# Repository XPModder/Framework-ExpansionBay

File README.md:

# Framework-ExpansionBay
Some stuff I made for the Framework Laptop 16 Expansion Bay

# Disclaimer
The Expansion Bay specification was created by Framework Computer Inc and published under Creative Commons BY 4.0 (http://creativecommons.org/licenses/by/4.0/)

All Contents of this repository are provided as-is. I take no responsibility for any damages caused to your device(s) by any content of this repository!

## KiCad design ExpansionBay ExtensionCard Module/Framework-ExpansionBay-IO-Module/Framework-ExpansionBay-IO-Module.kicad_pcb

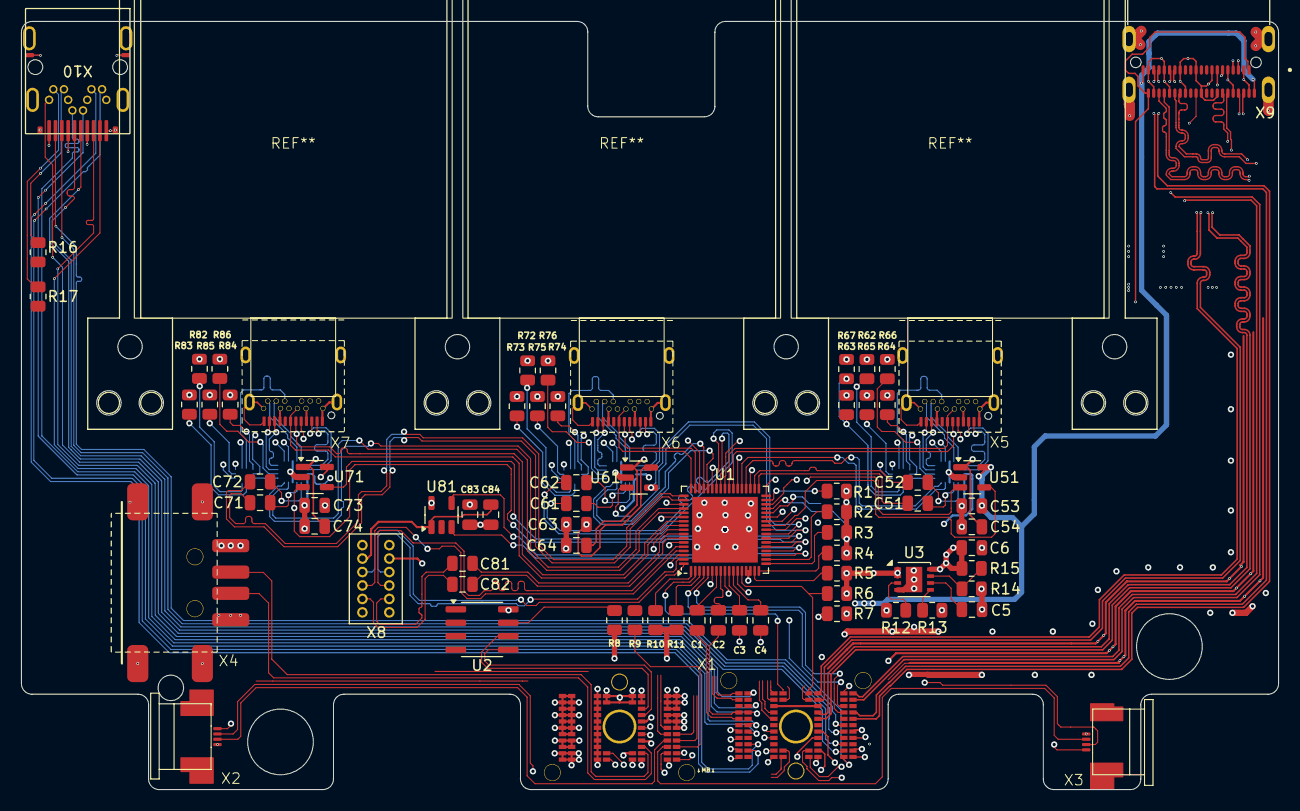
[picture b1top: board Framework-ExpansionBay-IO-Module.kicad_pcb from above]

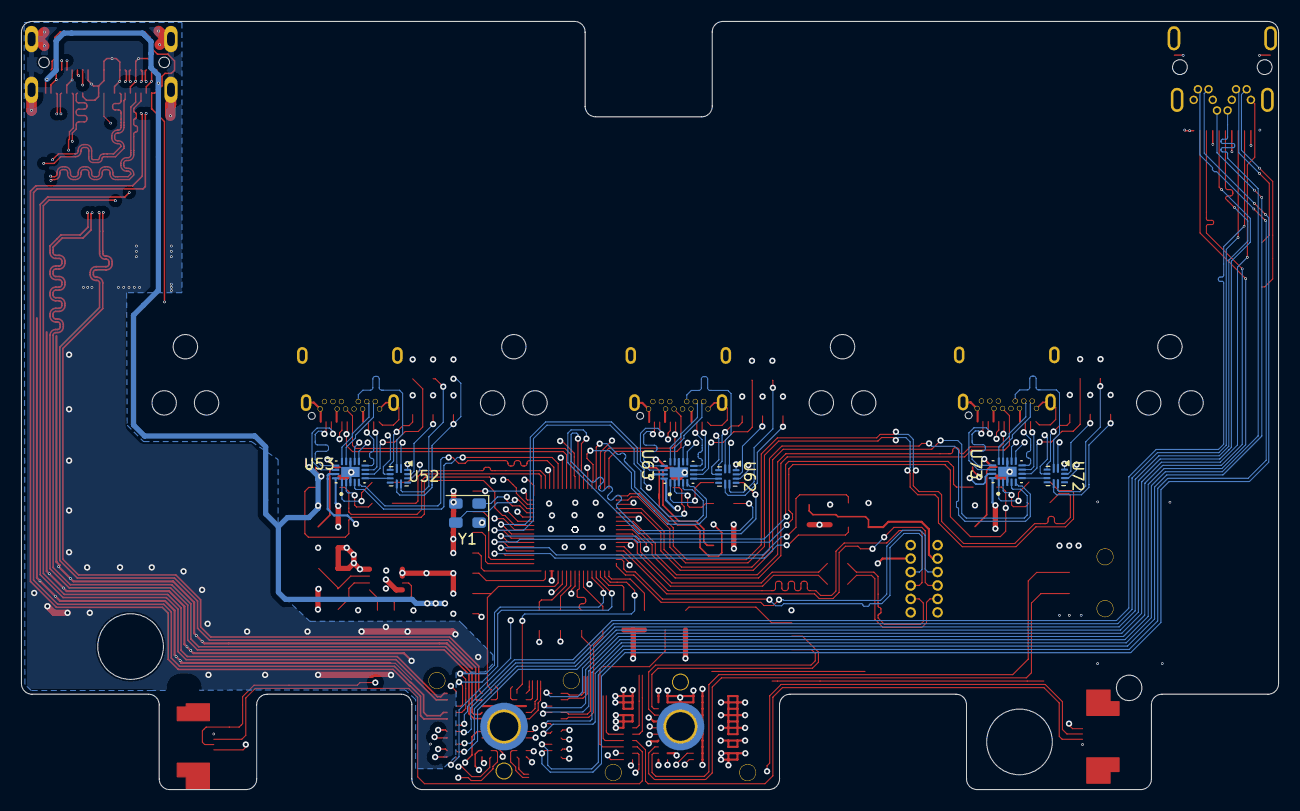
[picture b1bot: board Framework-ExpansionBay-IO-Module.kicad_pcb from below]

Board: 4 copper layers, 118.7 x 72.5 mm, 79 parts (7 on the bottom side), 164 nets.

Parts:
C1, C2, C3, C4, C51, C52, C53, C54, C61, C62, C63, C64, C71, C72, C73, C74, C81, C82, C83, C84: 100n; C_0805_2012Metric
C5, C6: 1u; C_0805_2012Metric
R1: 1k60; R_0805_2012Metric
R2, R3, R4, R6, R10, R11, R12, R13, R14, R16, R17: 10k; R_0805_2012Metric
R5: 47k; R_0805_2012Metric
R7, R9: 330k; R_0805_2012Metric
R8, R62, R63, R64, R65, R66, R67, R72, R73, R74, R75, R76, R82, R83, R84, R85, R86: 100k; R_0805_2012Metric
R15: 15k-16k; R_0805_2012Metric
U1: UPD720201K8-701-BAC-A; QFN-68-1EP_8x8mm_P0.4mm_EP6.2x6.2mm
U2: 24LC32A-I/SN; SOIC-8_3.9x4.9mm_P1.27mm
U3: MCP1727-ADJxMF; DFN-8-1EP_3x3mm_P0.65mm_EP1.55x2.4mm
U51, U61, U71, U81: XC8107; SOT-23-5
U52, U62, U72: FUSB303BTMX; Texas_X2QFN-12_1.6x1.6mm_P0.4mm
U53, U63, U73: FUSB340TMX; QFN40P200X280X40-19N
X1: Framework-FX-Beam
X2: Fan0; Molex-52746-0471
X3: Fan1; Molex-52746-0471
X4: USB_A; Würth-USB2-629104190121
X5, X6, X7: USB_C_Receptacle; Amphenol-USBC-10137062-00021LF
X8: Expansion-USB3; DS1015-02-12R6
X9: Molex-SFF8612-OcuLink-1719821142; MOLEX_1719821142
X10: FOXCONN 3VM11201-D730-7H; Mini DP FOXCONN 3VM11201-D730-7H
Y1: 24MHz; Crystal_SMD_EuroQuartz_MT-4Pin_3.2x2.5mm

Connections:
+1V0: C6.2, R15.2, U1.9 (VDD10), U1.12 (VDD10), U1.28 (VDD10), U1.37 (VDD10), U1.43 (VDD10), U1.46 (VDD10), U1.54 (VDD10), U1.60 (VDD10), U1.63 (VDD10), U3.8 (Vout)
+3V3: R5.2, R6.2, R8.2, R10.2, R11.2, R12.2, R13.2, R62.1, R63.2, R64.2, R72.1, R73.2, R74.2, R82.1, R83.2, R84.2, U1.6 (AVDD33), U1.14 (PONRSTB), U1.15 (VDD33), U1.29 (VDD33), U1.32 (AVDD33), U1.40 (VDD33), U1.49 (VDD33), U1.57 (VDD33), U1.66 (VDD33), U2.8 (VCC), U3.1 (Vin), U3.2 (Vin), U52.12 (VDD), U53.17 (VDD), U62.12 (VDD), U63.17 (VDD), U72.12 (VDD), U73.17 (VDD), X1.P-34 (3.3V_ALW), X1.P-35 (3.3V_ALW), X1.P-38 (3.3V_ALW), X1.P-39 (3.3V_ALW), X8.11, X9.A1 (3V3), X9.B21 (3V3), X10.20 (DP_PWR)
+5V: C53.2, C63.2, C73.2, C83.2, U51.5 (IN), U61.5 (IN), U71.5 (IN), U81.5 (IN), X1.P-10 (5V_ALW), X1.P-11 (5V_ALW), X1.P-21 (5V_ALW), X1.P-22 (5V_ALW), X4.1 (VBUS), X8.1, X8.12, X9.A21 (5V), X9.B1 (5V)
+12V: X1.P-41 (12V_Fan), X2.1, X3.1
DP_AUX+: X1.D-21 (DP_A_AUX), X10.16 (AUXp)
DP_AUX-: X1.D-20 (DP_A_AUX#), X10.18 (AUXn)
DP_HPD: X1.D-12 (DP_A_HPD), X10.2 (HPD)
DP_L0+: X1.D-18 (DP_A_L0), X10.12 (L3n(SRC)/L0p(SNK))
DP_L0-: X1.D-17 (DP_A_L0#), X10.10 (L3p(SRC)/L0n(SNK))
DP_L1+: X1.D-15 (DP_A_L1), X10.17 (L2n(SRC)/L1p(SNK))
DP_L1-: X1.D-14 (DP_A_L1#), X10.15 (L2p(SRC)/L1n(SNK))
DP_L2+: X1.D-62 (DP_A_L2), X10.11 (L1n(SRC)/L2p(SNK))
DP_L2-: X1.D-61 (DP_A_L2#), X10.9 (L1p(SRC)/L2n(SNK))
DP_L3+: X1.D-59 (DP_A_L3), X10.5 (L0n(SRC)/L3p(SNK))
DP_L3-: X1.D-58 (DP_A_L3#), X10.3 (L0p(SRC)/L3n(SNK))
Fan0_PWM: X1.P-60 (Fan0_SPEED), X2.3
Fan0_Speed: X1.P-37 (Fan0_PWM), X2.2
Fan1_PWM: X1.P-61 (Fan1_SPEED), X3.3
Fan1_Speed: X1.P-36 (Fan1_PWM), X3.2
GND: C5.1, C6.1, C53.1, C54.1, C63.1, C64.1, C73.1, C74.1, C83.1, C84.1, R1.1, R2.1, R3.1, R4.1, R7.2, R9.2, R14.1, R16.2, R17.2, R65.2, R66.2, R67.2, R75.2, R76.2, R85.2, R86.2, U1.34 (IC), U1.69 (GND), U2.1 (A0), U2.2 (A1), U2.3 (A2), U2.4 (GND), U3.4 (GND), U3.9 (GND), U51.2 (GND), U52.10 (GND), U53.3 (GND), U53.12 (GND), U53.18 (GND), U53.19 (EP), U61.2 (GND), U62.10 (GND), U63.3 (GND), U63.12 (GND), U63.18 (GND), U63.19 (EP), U71.2 (GND), U72.10 (GND), U73.3 (GND), U73.12 (GND), U73.18 (GND), U73.19 (EP), U81.2 (GND), X1.D-3 (GND), X1.D-6 (GND), X1.D-9 (GND), X1.D-13 (GND), X1.D-16 (GND), X1.D-19 (GND), X1.D-25 (GND), X1.D-28 (GND), X1.D-31 (GND), X1.D-44 (GND), X1.D-47 (GND), X1.D-50 (GND), X1.D-54 (GND), X1.D-57 (GND), X1.D-60 (GND), X1.D-66 (GND), X1.D-69 (GND), X1.D-72 (GND), X1.P-8 (GND), X1.P-9 (GND), X1.P-19 (GND), X1.P-20 (GND), X1.P-23 (GND), X1.P-24 (GND), X1.P-25 (GND), X1.P-26 (GND), X1.P-27 (GND), X1.P-28 (GND), X1.P-29 (GND), X1.P-30 (GND), X1.P-31 (GND), X1.P-32 (GND), X1.P-33 (GND), X1.P-40 (GND), X1.P-42 (GND), X1.P-43 (GND), X1.P-46 (GND), X1.P-49 (GND), X1.P-52 (GND), X1.P-56 (GND), X1.P-57 (GND), X1.P-67 (GND), X1.P-68 (GND), X1.P-69 (GND), X2.4, X3.4, X4.4 (GND), X4.5 (Shield), X5.A1 (GND), X5.A12 (GND), X5.B1 (GND), X5.B12 (GND), X5.S1 (SHIELD), X6.A1 (GND), X6.A12 (GND), X6.B1 (GND), X6.B12 (GND), X6.S1 (SHIELD), X7.A1 (GND), X7.A12 (GND), X7.B1 (GND), X7.B12 (GND), X7.S1 (SHIELD), X8.6, X8.7, X9.A2 (GND), X9.A5 (GND), X9.A8 (GND), X9.A11 (GND), X9.A14 (GND), X9.A17 (GND), X9.A20 (GND), X9.B2 (GND), X9.B5 (GND), X9.B8 (GND), X9.B11 (GND), X9.B14 (GND), X9.B17 (GND), X9.B20 (GND), X9.S1 (SHIELD), X9.S2 (SHIELD), X9.S3 (SHIELD), X9.S4 (SHIELD), X10.1 (GND), X10.7 (GND), X10.8 (GND), X10.13 (GND), X10.14 (GND), X10.19 (GND), X10.G (GND), Y1.2, Y1.4
I2C_SCL_EC: U2.6 (SCL), X1.P-44 (I2C_CLK_ALW)
I2C_SDA_EC: U2.5 (SDA), X1.P-45 (I2C_SDA_ALW)
unnamed: U1.26 (OCI1B), U51.3 (FLG)
unnamed: U1.24 (OCI2B), U61.3 (FLG)
unnamed: U1.22 (OCI3B), U71.3 (FLG)
unnamed: U1.20 (OCI4B), U81.3 (FLG)
unnamed: C2.2, U1.8 (PETXN)
unnamed: C1.2, U1.7 (PETXP)
unnamed: R11.1, U1.3 (PEWAKEB)
unnamed: U1.27 (PPON1), U51.4 (EN)
unnamed: U1.25 (PPON2), U61.4 (EN)
unnamed: U1.23 (PPON3), U71.4 (EN)
unnamed: U1.21 (PPON4), U81.4 (EN)
unnamed: R1.2, U1.33 (RREF)
unnamed: R10.1, U1.1 (SMIB)
unnamed: R4.2, U1.17 (SPICSB)
unnamed: R3.2, U1.18 (SPISCK)
unnamed: R2.2, U1.19 (SPISI)
unnamed: R5.1, U1.16 (SPISO)
unnamed: C52.1, U1.36 (U3TXDN1)
unnamed: C62.1, U1.45 (U3TXDN2)
unnamed: C72.1, U1.53 (U3TXDN3)
unnamed: C82.1, U1.62 (U3TXDN4)
unnamed: C51.1, U1.35 (U3TXDP1)
unnamed: C61.1, U1.44 (U3TXDP2)
unnamed: C71.1, U1.52 (U3TXDP3)
unnamed: C81.1, U1.61 (U3TXDP4)
unnamed: U1.31 (XT1), Y1.3
unnamed: U1.30 (XT2), Y1.1
unnamed: R8.1, U2.7 (WP)
unnamed: R14.2, R15.1, U3.7 (ADJ)
unnamed: C5.2, U3.6 (Cdelay)
unnamed: R13.1, U3.5 (PWRGD)
unnamed: R12.1, U3.3 (~SHDN)
unnamed: U52.5 (ADDR/ORIENT), U53.6 (S)
unnamed: R64.1, U52.3 (PORT/~DEBUG)
unnamed: R62.2, U52.8 (SCL/OUT2)
unnamed: R63.1, R67.1, U52.7 (SDA/OUT1)
unnamed: R65.1, U52.11 (~EN)
unnamed: R66.1, U53.7 (~OE)
unnamed: U62.5 (ADDR/ORIENT), U63.6 (S)
unnamed: R74.1, U62.3 (PORT/~DEBUG)
unnamed: R72.2, U62.8 (SCL/OUT2)
unnamed: R73.1, U62.7 (SDA/OUT1)
unnamed: R75.1, U62.11 (~EN)
unnamed: R76.1, U63.7 (~OE)
unnamed: U72.5 (ADDR/ORIENT), U73.6 (S)
unnamed: R84.1, U72.3 (PORT/~DEBUG)
unnamed: R82.2, U72.8 (SCL/OUT2)
unnamed: R83.1, U72.7 (SDA/OUT1)
unnamed: R85.1, U72.11 (~EN)
unnamed: R86.1, U73.7 (~OE)
unnamed: R9.1, X1.P-72 (ID0)
unnamed: R7.1, X1.D-63 (ID1)
unnamed: C4.2, X1.D-7 (PEX_TX0N)
unnamed: C3.2, X1.D-8 (PEX_TX0P)
unnamed: R17.1, X10.4 (CONFIG1)
unnamed: R16.1, X10.6 (CONFIG2)
PEX_CLK_RQ: R6.1, U1.13 (PECREQB), X1.D-38 (PEX_CLK_REQ#)
PEX_REFCLK: U1.4 (PECLKP), X1.D-55 (PEX_REFCLK)
PEX_REFCLK#: U1.5 (PECLKN), X1.D-56 (PEX_REFCLK#)
PEX_RST: U1.2 (PERSTB), X1.D-34 (PEX_RST#), X9.B12 (PERST#)
PEX_RX0+: C1.1, X1.D-5 (PEX_RX0P)
PEX_RX0-: C2.1, X1.D-4 (PEX_RX0N)
PEX_RX4+: X1.D-42 (PEX_RX4P), X9.A3 (PERp0)
PEX_RX4-: X1.D-43 (PEX_RX4N), X9.A4 (PERn0)
PEX_RX5+: X1.D-45 (PEX_RX5P), X9.A6 (PERp1)
PEX_RX5-: X1.D-46 (PEX_RX5N), X9.A7 (PERn1)
PEX_RX6+: X1.D-64 (PEX_RX6P), X9.A15 (PERp2)
PEX_RX6-: X1.D-65 (PEX_RX6N), X9.A16 (PERn2)
PEX_RX7+: X1.D-68 (PEX_RX7P), X9.A18 (PERp3)
PEX_RX7-: X1.D-67 (PEX_RX7N), X9.A19 (PERn3)
PEX_TX0+: C3.1, U1.10 (PERXP)
PEX_TX0-: C4.1, U1.11 (PERXN)
PEX_TX4+: X1.D-51 (PEX_TX4P), X9.B3 (PETp0)
PEX_TX4-: X1.D-52 (PEX_TX4N), X9.B4 (PETn0)
PEX_TX5+: X1.D-49 (PEX_TX5P), X9.B6 (PETp1)
PEX_TX5-: X1.D-48 (PEX_TX5N), X9.B7 (PETn1)
PEX_TX6+: X1.D-73 (PEX_TX6P), X9.B15 (PETp2)
PEX_TX6-: X1.D-74 (PEX_TX6N), X9.B16 (PETn2)
PEX_TX7+: X1.D-71 (PEX_TX7P), X9.B18 (PETp3)
PEX_TX7-: X1.D-70 (PEX_TX7N), X9.B19 (PETn3)
USB1_CC1: U52.1 (CC1), X5.A5 (CC1)
USB1_CC2: U52.2 (CC2), X5.B5 (CC2)
USB1_D+: U1.41 (U2DP1), X5.A6 (D+), X5.B6 (D+)
USB1_D-: U1.42 (U2DN1), X5.A7 (D-), X5.B7 (D-)
USB1_RX+: U1.38 (U3RXDP1), U53.5 (SSRXCOM+)
USB1_RX-: U1.39 (U3RXDN1), U53.4 (SSRXCOM-)
USB1_SSRX1+: U53.10 (SSRX1+), X5.B11 (RX1+)
USB1_SSRX1-: U53.11 (SSRX1-), X5.B10 (RX1-)
USB1_SSRX2+: U53.8 (SSRX2+), X5.A11 (RX2+)
USB1_SSRX2-: U53.9 (SSRX2-), X5.A10 (RX2-)
USB1_SSTX1+: U53.15 (SSTX1+), X5.A2 (TX1+)
USB1_SSTX1-: U53.16 (SSTX1-), X5.A3 (TX1-)
USB1_SSTX2+: U53.13 (SSTX2+), X5.B2 (TX2+)
USB1_SSTX2-: U53.14 (SSTX2-), X5.B3 (TX2-)
USB1_TX+: C51.2, U53.2 (SSTXCOM+)
USB1_TX-: C52.2, U53.1 (SSTXCOM-)
USB1_VBUS: C54.2, U51.1 (OUT), U52.4 (VBUS_DET), X5.A4 (VBUS), X5.A9 (VBUS), X5.B4 (VBUS), X5.B9 (VBUS)
USB2_CC1: U62.1 (CC1), X6.A5 (CC1)
USB2_CC2: U62.2 (CC2), X6.B5 (CC2)
USB2_D+: U1.50 (U2DP2), X6.A6 (D+), X6.B6 (D+)
USB2_D-: U1.51 (U2DN2), X6.A7 (D-), X6.B7 (D-)
USB2_RX+: U1.47 (U3RXDP2), U63.5 (SSRXCOM+)
USB2_RX-: U1.48 (U3RXDN2), U63.4 (SSRXCOM-)
USB2_SSRX1+: U63.10 (SSRX1+), X6.B11 (RX1+)
USB2_SSRX1-: U63.11 (SSRX1-), X6.B10 (RX1-)
USB2_SSRX2+: U63.8 (SSRX2+), X6.A11 (RX2+)
USB2_SSRX2-: U63.9 (SSRX2-), X6.A10 (RX2-)
USB2_SSTX1+: U63.15 (SSTX1+), X6.A2 (TX1+)
USB2_SSTX1-: U63.16 (SSTX1-), X6.A3 (TX1-)
USB2_SSTX2+: U63.13 (SSTX2+), X6.B2 (TX2+)
USB2_SSTX2-: U63.14 (SSTX2-), X6.B3 (TX2-)
USB2_TX+: C61.2, U63.2 (SSTXCOM+)
USB2_TX-: C62.2, U63.1 (SSTXCOM-)
USB2_VBUS: C64.2, U61.1 (OUT), U62.4 (VBUS_DET), X6.A4 (VBUS), X6.A9 (VBUS), X6.B4 (VBUS), X6.B9 (VBUS)
USB3_CC1: U72.1 (CC1), X7.A5 (CC1)
USB3_CC2: U72.2 (CC2), X7.B5 (CC2)
USB3_D+: U1.58 (U2DP3), X7.A6 (D+), X7.B6 (D+)
USB3_D-: U1.59 (U2DN3), X7.A7 (D-), X7.B7 (D-)
USB3_RX+: U1.55 (U3RXDP3), U73.5 (SSRXCOM+)
USB3_RX-: U1.56 (U3RXDN3), U73.4 (SSRXCOM-)
USB3_SSRX1+: U73.10 (SSRX1+), X7.B11 (RX1+)
USB3_SSRX1-: U73.11 (SSRX1-), X7.B10 (RX1-)
USB3_SSRX2+: U73.8 (SSRX2+), X7.A11 (RX2+)
USB3_SSRX2-: U73.9 (SSRX2-), X7.A10 (RX2-)
USB3_SSTX1+: U73.15 (SSTX1+), X7.A2 (TX1+)
USB3_SSTX1-: U73.16 (SSTX1-), X7.A3 (TX1-)
USB3_SSTX2+: U73.13 (SSTX2+), X7.B2 (TX2+)
USB3_SSTX2-: U73.14 (SSTX2-), X7.B3 (TX2-)
USB3_TX+: C71.2, U73.2 (SSTXCOM+)
USB3_TX-: C72.2, U73.1 (SSTXCOM-)
USB3_VBUS: C74.2, U71.1 (OUT), U72.4 (VBUS_DET), X7.A4 (VBUS), X7.A9 (VBUS), X7.B4 (VBUS), X7.B9 (VBUS)
USB4_D+: U1.67 (U2DP4), X8.10
USB4_D-: U1.68 (U2DN4), X8.3
USB4_RX+: U1.64 (U3RXDP4), X8.9
USB4_RX-: U1.65 (U3RXDN4), X8.4
USB4_TX+: C81.2, X8.8
USB4_TX-: C82.2, X8.5
USB4_VBUS: C84.2, U81.1 (OUT), X8.2
USB-MB+: X1.P-50 (USB+), X4.3 (D+)
USB-MB-: X1.P-51 (USB-), X4.2 (D-)
VADP: X1.P-53 (VADP_GPU), X1.P-54 (VADP_GPU), X1.P-55 (VADP_GPU), X1.P-64 (VADP_GPU), X1.P-65 (VADP_GPU), X1.P-66 (VADP_GPU)
VSys: X1.P-1 (VSYS_GPU), X1.P-2 (VSYS_GPU), X1.P-3 (VSYS_GPU), X1.P-4 (VSYS_GPU), X1.P-5 (VSYS_GPU), X1.P-6 (VSYS_GPU), X1.P-7 (VSYS_GPU), X1.P-12 (VSYS_GPU), X1.P-13 (VSYS_GPU), X1.P-14 (VSYS_GPU), X1.P-15 (VSYS_GPU), X1.P-16 (VSYS_GPU), X1.P-17 (VSYS_GPU), X1.P-18 (VSYS_GPU)

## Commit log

2024-04-06 Add expansion bay module KiCad schematic and pcb layout
2024-04-06 Add expansion bay KiCad footprints
2024-04-06 add expansion bay KiCad symbols
2024-04-19 added schematics and board for extension card module
2025-12-17 partial redesign
